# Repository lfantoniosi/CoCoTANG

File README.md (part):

# CoCoTANG

## Overview

CoCoTANG upgrades the Radio Shack/Tandy Color Computer 1 and 2 with a Tang Nano 20K FPGA board and CoCo 3 video and memory features. It retains the MC6809E CPU and motherboard PIAs while the FPGA implements the GIME video and memory subsystem, HDMI and analog video outputs, and a Glenside-compatible IDE interface backed by a microSD card. It also provides 8 MB of RAM, Orchestra-90 audio with stereo over HDMI, and Tandy Speech/Sound Cartridge (SSC) support.

This repository contains the FPGA sources, KiCad designs, fabrication files, and bill of materials.

The assembly uses a **main board** for the CPU and Tang Nano 20K, **PIA0 and PIA1 adapter boards**, and an **address mux board** that replaces the motherboard 74LS138. An **analog video hat** and an **HDB-DOS ROM cartridge** are optional. The render above shows the boards arranged as a PCB panel. HDB-DOS can also be supplied through an FD-502 ROM socket or CoCo SDC flash bank.

The design uses NTSC machine clocking. The GIME's 50 Hz setting remains available, but selecting it does **not** switch to a PAL crystal. PAL-encoded CVBS/S-Video output is also supported. See [Build on macOS or Linux](#build-on-macos-or-linux) for video targets and the [FPGA pin and bus map](fpga/docs/pinout.md) for hardware connections.

## Compatibility

### Color Computer 1 power-supply noise

CoCoTANG has been confirmed working on a Color Computer 1 with added power-supply decoupling: **a 100 µF electrolytic capacitor and a 100 nF ceramic capacitor connected in parallel across the supply**, as shown below. This resolves the power-supply noise that previously caused rolling video interference and intermittent loss of analog sync, and also appeared to affect HDMI.

### Games

So far, **The Contras is the only game found to fail to load in its original form**. CoCoTANG's **262.5-scanline timing drifts relative to the original CoCo 3**. The resulting timing difference affects an unprotected code section in the game and prevents the original version from loading.

Use the [patched version of The Contras](https://drive.google.com/file/d/1ANGJpljmbaEt34lFBowtTOSvq0qSiGtF/view?usp=sharing) instead. This patched version also includes **keyboard enhancements**.

### Multi-Pak Interface and real floppy drives

A **Multi-Pak Interface (MPI)** holds the cartridge data bus in a way that prevents access to CoCoTANG's internal peripheral registers. With an MPI connected, the **internal Glenside IDE, SSC sound/speech, and Orchestra-90 are unavailable**. Software that uses these internal devices must be run without the MPI.

**An MPI is required to use real floppy drives.** Plug the floppy disk controller into the MPI and connect the drives to that controller. This setup uses the external floppy controller, with the internal IDE, SSC, and Orchestra-90 unavailable as described above.

## Current FPGA features

- GIME video and memory mapping with 8 MB NoCan3-style RAM support and readable Disto MMU page bits.
- Simultaneous HDMI and analog video, with separate RGB, YPbPr, and CVBS/S-Video build targets.
- Six motherboard RESET selections combining normal, reversed, or disabled artifact colours with SSC sound/speech off or on.
- Tandy Speech/Sound Cartridge PSG, buffered allophones, and ASCII English text-to-speech, alongside the CoCo DAC and Orchestra-90 audio.
- HDMI status labels and an optional analog status banner with a larger font.

## Hardware and files

| Item | File or notes |
| --- | --- |
| PCB fabrication files | [Gerber/drill ZIPs for each board](kicad/gerber/) |
| KiCad schematic and PCB | [kicad/](kicad/) |
| Components | Full bill of materials below |
| FPGA project and sources | [fpga/](fpga/) |
| FPGA pin/bus map | [fpga/docs/pinout.md](fpga/docs/pinout.md) |

## Board quantities and Gerber downloads

For one CoCoTANG installation, you need **one main board, one address mux board, and two PIA boards**: one for PIA0 and one for PIA1. There are two main-board versions, for motherboard revisions **20261043** and **20261058**; choose the version that matches your motherboard. The HDB-DOS cartridge and video hat are optional.

| Board | Quantity per installation | Gerber/drill ZIP |
| --- | --- | --- |
| Main board (CPU / Tang Nano 20K) | 1 required; choose the matching version | See the compatibility table below |
| Address mux (addrmux) | 1 required | [gerber_addrmux.zip](kicad/gerber/gerber_addrmux.zip) |
| PIA card | 2 required: PIA0 and PIA1 | [gerber_pia.zip](kicad/gerber/gerber_pia.zip) |
| HDB-DOS cartridge | 1 optional | [gerber_cart.zip](kicad/gerber/gerber_cart.zip) |
| Video hat | 1 optional | [gerber_avideo.zip](kicad/gerber/gerber_avideo.zip) |
| External keyboard extension | 1 optional | [gerber_extkey.zip](kicad/gerber/gerber_extkey.zip) |

Use the same PIA Gerber ZIP to fabricate both PIA cards. Upload each desired board's ZIP separately to your PCB manufacturer and select the quantities above, subject to the manufacturer's minimum order quantity.

Select **1.2 mm PCB thickness** when ordering the adapter boards. The thinner boards reduce the installed profile and help the assembly fit under the keyboard.

## Motherboard compatibility

Tandy used several motherboard layouts for the CoCo 2. Identify your motherboard before ordering boards: the CPU and address mux adapters must fit its layout. Only the revisions marked compatible below are currently supported; other layouts may need different adapters.

| Motherboard revision | Compatible | Main board Gerber ZIP |
| --- | --- | --- |
| [20261043](fpga/docs/20261043.jpg) | Yes | [gerber_main_20261043.zip](kicad/gerber/gerber_main_20261043.zip) |
| [20261058](fpga/docs/20261058.jpg) | Yes | [gerber_main_20261058.zip](kicad/gerber/gerber_main_20261058.zip) |
| [20261044](fpga/docs/20261044.jpg) | No | — |
| [20261045](fpga/docs/20261045.jpg) | No | — |
| [20261059](fpga/docs/20261059.jpg) | No | — |

**CoCo 1 operation is confirmed with added 100 µF + 100 nF supply decoupling.** See the [decoupling details and installation photo](#color-computer-1-power-supply-noise).

## Bill of materials

Both main-board versions (**20261043** and **20261058**) use the same components and quantities; only the PCB layout differs. Use the fabrication drawing and silkscreen for the version you are assembling.

### Logic families and supply voltages

Use **HCT** parts for the 5 V logic: U9/U16 (74HCT245, depending on the main-board version), U1 (74HCT138), U22 (74HCT11), and U7 (74HCT30). Their TTL-compatible inputs accept the logic levels used at the motherboard interface. The table below gives the manufacturer part numbers, matching DigiKey part numbers, and TSSOP packages.

**U3/U6 are 74HC139 decoders powered from 3.3 V**, with their select inputs driven by the FPGA. Keep the HC version here: [74HCT139 is specified for a 4.5–5.5 V supply](https://assets.nexperia.com/documents/data-sheet/74HC_HCT139.pdf). A 3.3 V supply makes HC139 suitable for this 3.3 V logic domain; it does not turn HC into a generally TTL-compatible family. The KiCad labels now identify both decoder instances as HC139.

The four **74LVC245** buffers on each main board remain LVC parts for the 3.3 V interface; their reference designators are listed for both layouts below. Their TSSOP ordering code is **SN74LVC245APWR**.

### Main board — both versions

The reference columns identify the same components on each layout. Lists follow the same order across both columns. The three interrupt/reset resistors and the additional R/W pull-up are listed separately. The other adapter boards below are shared between both versions.

| Qty | Value | Description | DigiKey P/N | 20261043 references | 20261058 references | Alternative link |
| ---: | --- | --- | --- | --- | --- | --- |
| 1 | Tang Nano 20K | Tang Nano 20K FPGA Board | N/A | U5 | U17 | [AliExpress](https://www.aliexpress.com/item/1005010280135538.html) |
| 6 | 0.1 µF | CAP CER 0805 0.1UF 100VDC X7R | [399-C0805F104K1RACAUTOCT-ND](https://www.digikey.com/en/products/detail/kemet/C0805F104K1RACAUTO/26735352) | C2, C3, C4, C5, C6, C7 | C13, C16, C19, C14, C18, C15 |  |
| 3 | MMBT3904-TP | TRANS NPN 40V 0.2A SOT-23 | [MMBT3904TPMSCT-ND](https://www.digikey.com/en/products/detail/mcc-micro-commercial-components/MMBT3904-TP/717280) | Q7, Q8, Q9 | Q1, Q3, Q6 |  |
| 1 | SS14 | DIODE SCHOTTKY 40V 1A DO214AC | [SS14CT-ND](https://www.digikey.com/en/products/detail/onsemi/SS14/965474) | D2 | D4 |  |
| 3 | 10K | RES 10K OHM 1% 1/8W 0805 | [311-10.0KCRCT-ND](https://www.digikey.com/en/products/detail/yageo/RC0805FR-0710KL/727535) | R2, R4, R6 | R14, R18, R15 |  |
| 3 | 4.7K | RES 4.7K OHM 1% 1/8W 0805 | [311-4.70KCRCT-ND](https://www.digikey.com/en/products/detail/yageo/RC0805FR-074K7L/730876) | R3, R5, R7 | R20, R22, R21 |  |
| 1 | 4.7K | R/W pull-up, 1% 1/8W 0805 | [311-4.70KCRCT-ND](https://www.digikey.com/en/products/detail/yageo/RC0805FR-074K7L/730876) | R19 | R13 |  |
| 2 | 47K | RES SMD 47K OHM 1% 1/8W 0805 | [YAG3735CT-ND](https://www.digikey.com/en/products/detail/yageo/AC0805FR-0747KL/6006584) | R8, R9 | R25, R26 |  |
| 2 | 4.7K | RES ARRAY 8 RES 4.7K OHM 9SIP | [4609X-101-472LF-ND](https://www.digikey.ca/en/products/detail/bourns-inc/4609X-101-472LF/3593671) | RN1, RN2 | RN4, RN3 |  |
| 4 | SN74LVC245APWR | 8-bit bus transceiver, 1.65–3.6 V, TSSOP-20 | [296-1233-1-ND](https://www.digikey.com/en/products/detail/texas-instruments/SN74LVC245APWR/276501) | U8, U10, U11, U12 | U4, U13, U15, U14 |  |
| 1 | SN74HCT245PWR | 8-bit bus transceiver, TTL inputs, 4.5–5.5 V, TSSOP-20 | [296-8404-1-ND](https://www.digikey.com/en/products/detail/texas-instruments/SN74HCT245PWR/376998) | U9 | U16 |  |
| 1 | 74HC139PW,118 | Dual 2-to-4 decoder, CMOS inputs, 2–6 V; used at 3.3 V, TSSOP-16 | [1727-6580-1-ND](https://www.digikey.com/en/products/detail/nexperia-usa-inc/74HC139PW-118/2813773) | U3 | U6 |  |
| 1 | SIL FEMALE HDR | MACHINE PIN SOCKET 40P 2.54MM PI | [SMC-1A-40-1-GT-HT](https://www.digikey.com/en/products/detail/adam-tech/SMC-1A-40-1-GT-HT/9831942) | U5 | U17 | [AliExpress](https://www.aliexpress.com/item/1005008648234734.html) |
| 1 | DIP-40 SOCKET | MACHINE PIN SOCKET, IC, DIP, 40P | [ICM-640-1-GT-HT](https://www.digikey.com/en/products/detail/adam-tech/ICM-640-1-GT-HT/9832971) | J1 | J19 | [AliExpress](https://www.aliexpress.com/item/1005006139495909.html) |

### PIA0 adapter

| Qty | Value | Description | DigiKey P/N | References | Alternative link |
| ---: | --- | --- | --- | --- | --- |
| 1 | 0.1 µF | CAP CER 0805 0.1UF 100VDC X7R | [399-C0805F104K1RACAUTOCT-ND](https://www.digikey.com/en/products/detail/kemet/C0805F104K1RACAUTO/26735352) | C1 | |
| 1 | DIP-40 SOCKET | MACHINE PIN SOCKET, IC, DIP, 40P | [ICM-640-1-GT-HT](https://www.digikey.com/en/products/detail/adam-tech/ICM-640-1-GT-HT/9832971) | J4 | [AliExpress](https://www.aliexpress.com/item/1005006139495909.html) |
| 1 | 74HCT30PW,118 | 8-input NAND gate, TTL inputs, 4.5–5.5 V, TSSOP-14 | [1727-6632-1-ND](https://www.digikey.com/en/products/detail/nexperia-usa-inc/74HCT30PW-118/1230819) | U7 | |
| 2 | 1,800 pF | CAP CER 1800PF 250V C0G/NP0 0805 | [490-GCM21A5C2E182FX01DCT-ND](https://www.digikey.ca/en/products/detail/murata-electronics/GCM21A5C2E182FX01D/17845644) | C10,C12 | |
| 2 | SD103BW | DIODE SCHOTTKY 30V 0.35A SOD123F | [4878-SD103BWCT-ND](https://www.digikey.com/en/products/detail/diotec-semiconductor/SD103BW/22600375) | D1,D3 | |

### PIA1 adapter

| Qty | Value | Description | DigiKey P/N | References | Alternative link |
| ---: | --- | --- | --- | --- | --- |
| 1 | DIP-40 SOCKET | MACHINE PIN SOCKET, IC, DIP, 40P | [ICM-640-1-GT-HT](https://www.digikey.com/en/products/detail/adam-tech/ICM-640-1-GT-HT/9832971) | J4 | [AliExpress](https://www.aliexpress.com/item/1005006139495909.html) |

### Address mux board

| Qty | Value | Description | DigiKey P/N | References | Alternative link |
| ---: | --- | --- | --- | --- | --- |
| 2 | 0.1 µF | CAP CER 0805 0.1UF 100VDC X7R | [399-C0805F104K1RACAUTOCT-ND](https://www.digikey.com/en/products/detail/kemet/C0805F104K1RACAUTO/26735352) | C32,C33 | |
| 1 | SN74HCT138PWR | 3-to-8 decoder, TTL inputs, 4.5–5.5 V, TSSOP-16 | [296-8388-1-ND](https://www.digikey.com/en/products/detail/texas-instruments/SN74HCT138PWR/377055) | U1 | |
| 1 | 74HCT11PW,118 | Triple 3-input AND gate, TTL inputs, 4.5–5.5 V, TSSOP-14 | [1727-7964-1-ND](https://www.digikey.com/en/products/detail/nexperia-usa-inc/74HCT11PW-118/1230602) | U22 | |
| 1 | DIP-16 SOCKET | CONN IC DIP SOCKET 16POS GOLD | [SA163000](https://www.digikey.com/en/products/detail/on-shore-technology-inc/SA163000/3313525) | J28 | [AliExpress](https://www.aliexpress.com/item/32866483409.html) |

### HDB-DOS cartridge

| Qty | Value | Description | DigiKey P/N | References | Alternative link |
| ---: | --- | --- | --- | --- | --- |
| 1 | DIP-28 SOCKET | CONN IC DIP SOCKET 28POS GOLD | [110-41-628-41-001000](https://www.digikey.com/en/products/detail/mill-max-manufacturing-corp/110-41-628-41-001000/2538108) | U2 | [AliExpress](https://www.aliexpress.com/item/32866483409.html) |
| 1 | 0.1 µF | CAP CER 0805 0.1UF 100VDC X7R | [399-C0805F104K1RACAUTOCT-ND](https://www.digikey.com/en/products/detail/kemet/C0805F104K1RACAUTO/26735352) | C34 | |
| 1 | AT28C64B-15PU | IC EEPROM 64KBIT PARALLEL 28DIP | [AT28C64B-15PU-ND](https://www.digikey.com/en/products/detail/microchip-technology/AT28C64B-15PU/1008529) | U2 | |

### Analog video board

| Qty | Value | Description | DigiKey P/N | References | Alternative link |
| ---: | --- | --- | --- | --- | --- |
| 3 | 0.1 µF | CAP CER 0805 0.1UF 100VDC X7R | [399-C0805F104K1RACAUTOCT-ND](https://www.digikey.com/en/products/detail/kemet/C0805F104K1RACAUTO/26735352) | C29,C30,C31 | |
| 3 | 470 pF | CAP CER 470PF 50V C0G/NP0 0805 | [490-1617-1-ND](https://www.digikey.com/en/products/detail/murata-electronics/GRM2165C1H471JA01D/587515) | C8,C9,C11 | |
| 1 | 1 µF | CAP CER 1UF 25V X7R 0805 | [399-C0805C105K3RACTUCT-ND](https://www.digikey.com/en/products/detail/kemet/C0805C105K3RACTU/3471727) | C15 | |
| 6 | 1K | RES 1K OHM 1% 1/8W 0805 | [541-3977-1-ND](https://www.digikey.com/en/products/detail/vishay-dale/CRCW08051K00FKEAC/7928660) | R31,R17,R33,R1,R35,R16 | |
| 3 | 75 | RES 75 OHM 1% 1/8W 0805 | [541-CRCW080575R0FKEACCT-ND](https://www.digikey.com/en/products/detail/vishay-dale/CRCW080575R0FKEAC/12745060) | R10,R11,R12 | |
| 3 | 4.7K | RES 4.7K OHM 1% 1/8W 0805 | [311-4.70KCRCT-ND](https://www.digikey.com/en/products/detail/yageo/RC0805FR-074K7L/730876) | R32,R34,R36 | |
| 1 | 6.8 nF | CAP CER 6800PF 250V C0G/NP0 0805 | [490-GCM21B5C2E682JX0ALCT-ND](https://www.digikey.com/en/products/detail/murata-electronics/GCM21B5C2E682JX0AL/17846799) | C24 | |
| 1 | 4.7 µF | CAP CER 4.7UF 16V X7R 0805 | [732-7666-1-ND](https://www.digikey.com/en/products/detail/w%C3%BCrth-elektronik/885012207053/5453521) | C25 | |
| 1 | 100K | RES 100K OHM 1% 1/8W 0805 | [541-3978-1-ND](https://www.digikey.com/en/products/detail/vishay-dale/CRCW0805100KFKEAC/7928661) | R24 | |
| 3 | MMBT3904-TP | TRANS NPN 40V 0.2A SOT-23 | [MMBT3904TPMSCT-ND](https://www.digikey.com/en/products/detail/mcc-micro-commercial-components/MMBT3904-TP/717280) | Q2,Q4,Q5 | |
| 1 | DIN-5 FEMALE | D5 PIN DIN SOCKET 180 DEGREE | [4654-FC680805-ND](https://www.digikey.ca/en/products/detail/cliff-electronic-components-ltd/FC680805/24420883) | J24 | [AliExpress](https://www.aliexpress.com/item/32981543684.html)|

## Boards Interconnection
| Qty | Value | Description | DigiKey P/N | References | Alternative link |
| ---: | --- | --- | --- | --- | --- |
| 2 | PRPC040SBAN-M71RC | CONN HEADER R/A 40POS 2.54MM | [S1111EC-40-ND](https://www.digikey.ca/en/products/detail/sullins-connector-solutions/PRPC040SBAN-M71RC/2775294) | 
| 2 |1950 | JUMPER WIRE F TO F 6" 28AWG | [1528-1961-ND](https://www.digikey.ca/en/products/detail/adafruit-industries-llc/1950/6827084)

*NOTE:* You may need more than one jumper wires pack or source at different place like Amazon. CoCo1 requires longer jumper wires  

## Assembly

Print the [fabrication drawing](fpga/docs/fab.pdf) and use it with the board silkscreen to identify component positions. Check diode orientation before soldering. The main-board bill of materials applies to both supported versions; component positions differ between layouts.

Several adapters have oversized socket holes. They require machined-pin sockets whose pins extend through the adapter to connect to the motherboard socket while holding the original IC above it. Use 1.2 mm PCBs to reduce the overall assembly height and improve clearance under the keyboard.

1. Locate and desolder the CPU, VDG, SAM, PIA0, PIA1, and 74LS138.
2. Keep the SAM, VDG, and 74LS138 as spares; the FPGA replaces their functions.
3. Install sockets in the motherboard. Do not solder the adapter boards directly to it.
4. Check clearance around the adapters. Some original capacitors marked `104` are oversized, and nearby radial capacitors may also interfere. Where necessary, desolder and reposition their leads before bending the capacitors closer to the motherboard.
5. Populate the adapter boards, checking diode orientation. Configure each PIA adapter as described in [PIA adapter configuration](#pia-adapter-configuration).
6. Modify pin 5 of each joystick connector and wire it to the PIA0 adapter as described in [Joystick second-button support](#joystick-second-button-support).
7. Fit the CPU and PIAs to their adapters, install the adapters, and connect the boards as shown in the [installed prototype](fpga/docs/installed_prototype.jpg).
8. Program the Tang Nano 20K with the desired `.fs` bitstream and CoCo 3 ROM, following the programming instructions below.
9. If using the optional HDB-DOS cartridge, program its EEPROM with [hdblba.rom](fpga/roms/hdblba.rom) using an EEPROM programmer.
10. Turn on the computer. The boot screen should look like the example below.

### Assembled boards

The photos below show the component population and header placement, in assembly order. Front and back views are included where available.

#### Main board

The main board carries the CPU socket, Tang Nano 20K headers, bus buffers, and connections to the other adapters. The photos show the assembled board before fitting the CPU and FPGA module. Choose the layout that matches your motherboard revision.

| Front | Back |
| --- | --- |
|  |  |

#### ADDRMUX board

The address mux adapter plugs into the motherboard's former **74LS138** position and connects to the main board. **Leave the 74LS138 socket on the ADDRMUX adapter empty; do not reinstall the original IC in it.** The adapter's onboard logic replaces its function.

#### PIA0 adapter

Populate the logic IC, diodes, capacitors, and headers required for PIA0, and select the **PIA0** jumper setting. The external keyboard header is fitted only on this adapter. These photos show the board before installing the PIA.

| Front | Back |
| --- | --- |
|  |  |

#### PIA1 adapter

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
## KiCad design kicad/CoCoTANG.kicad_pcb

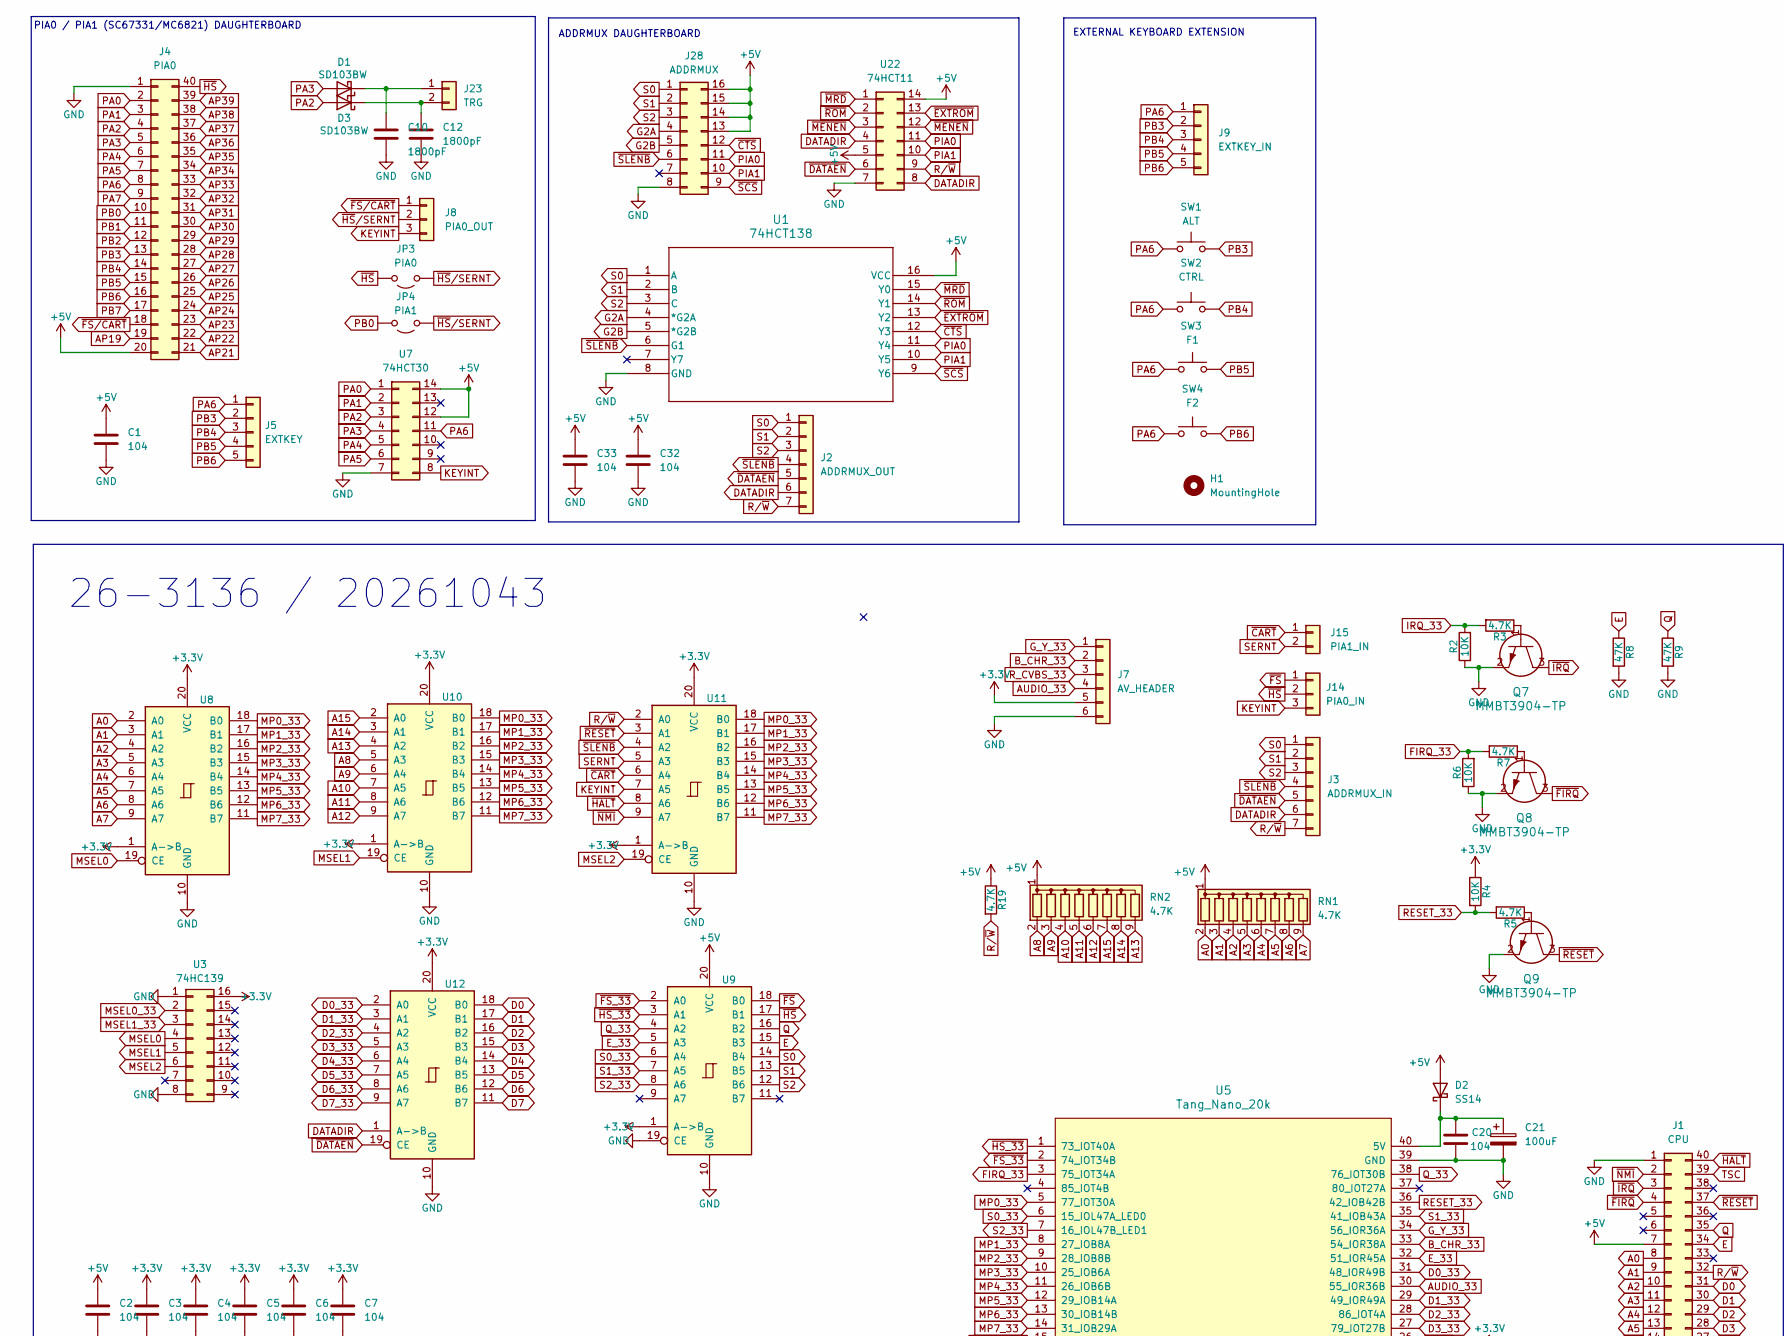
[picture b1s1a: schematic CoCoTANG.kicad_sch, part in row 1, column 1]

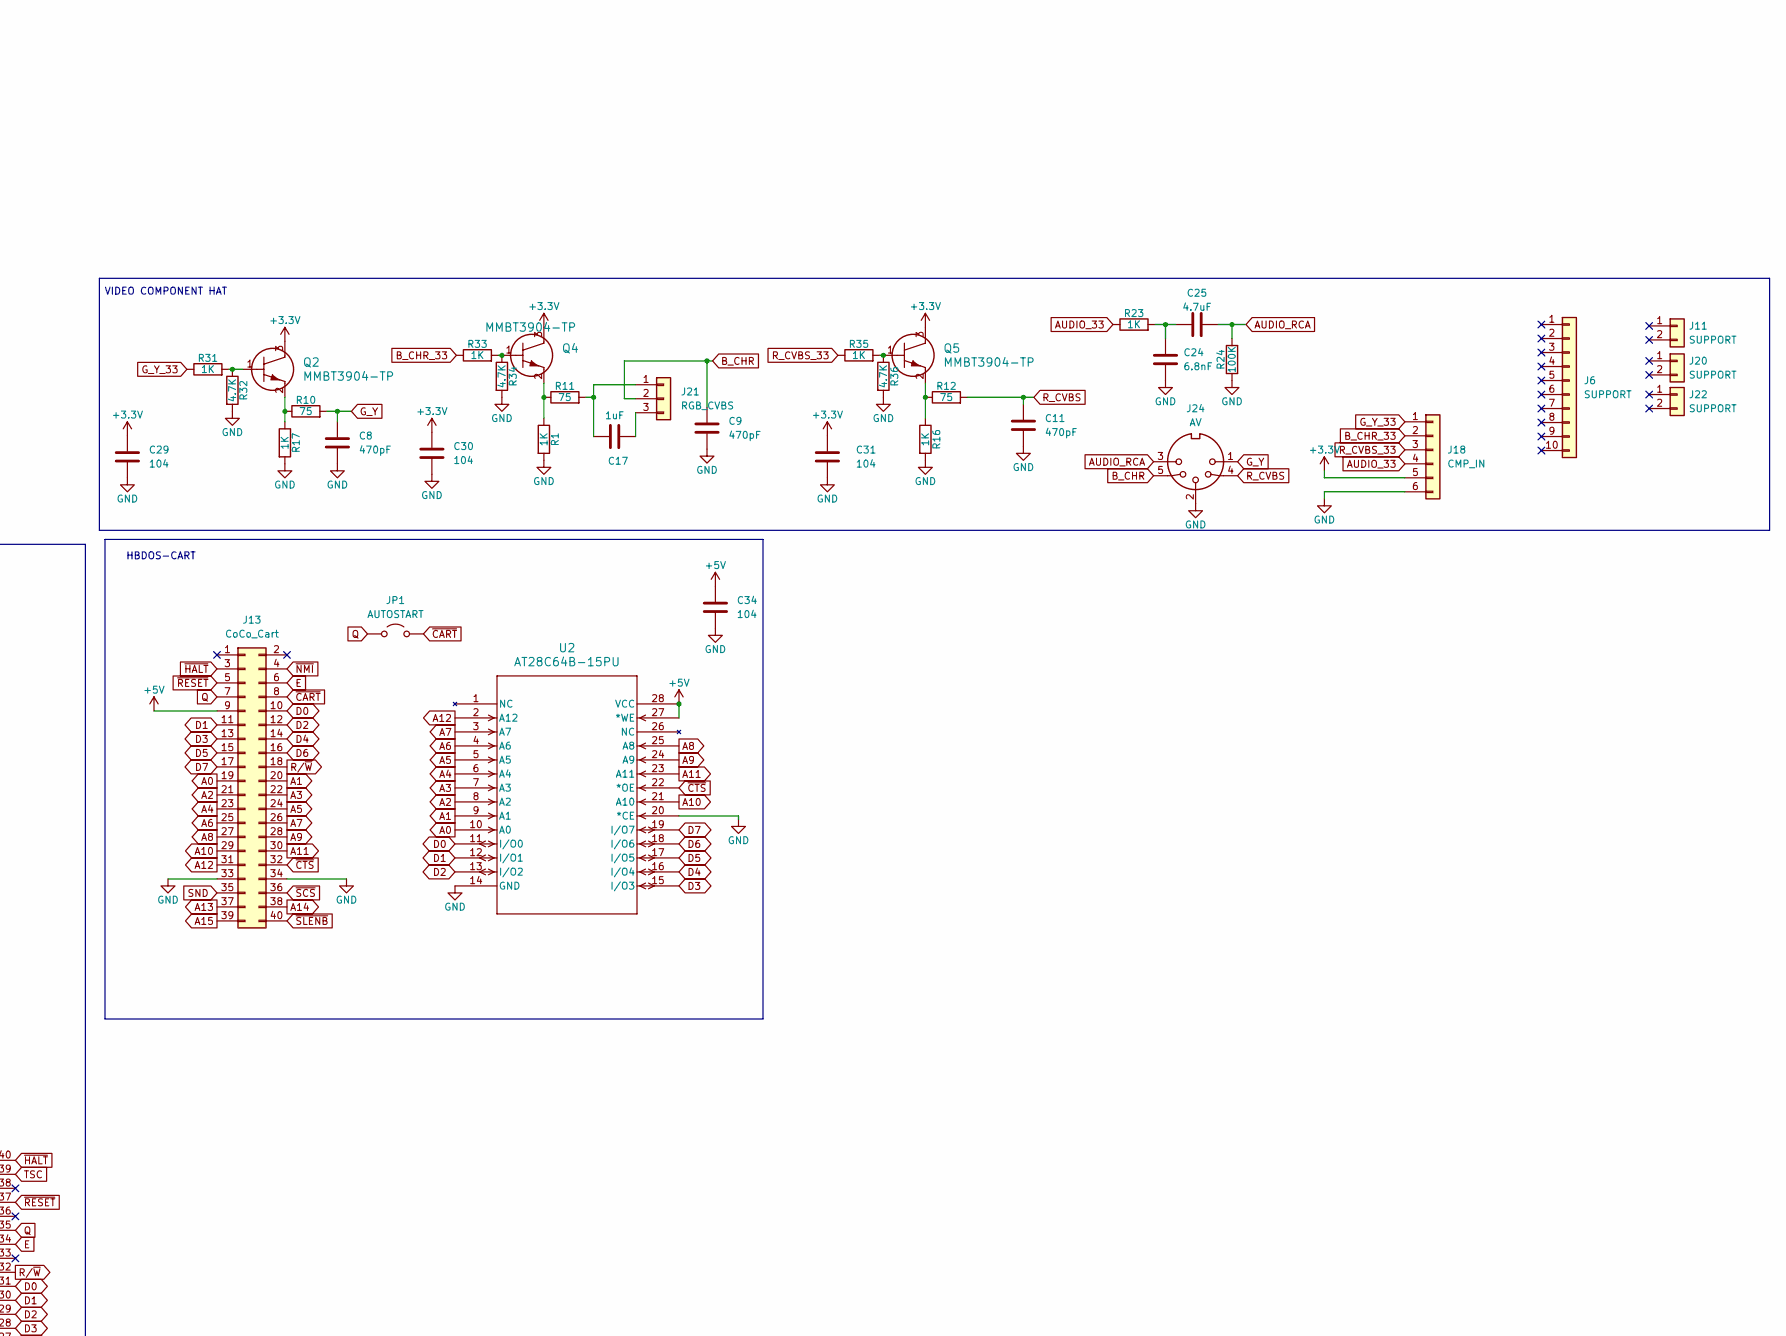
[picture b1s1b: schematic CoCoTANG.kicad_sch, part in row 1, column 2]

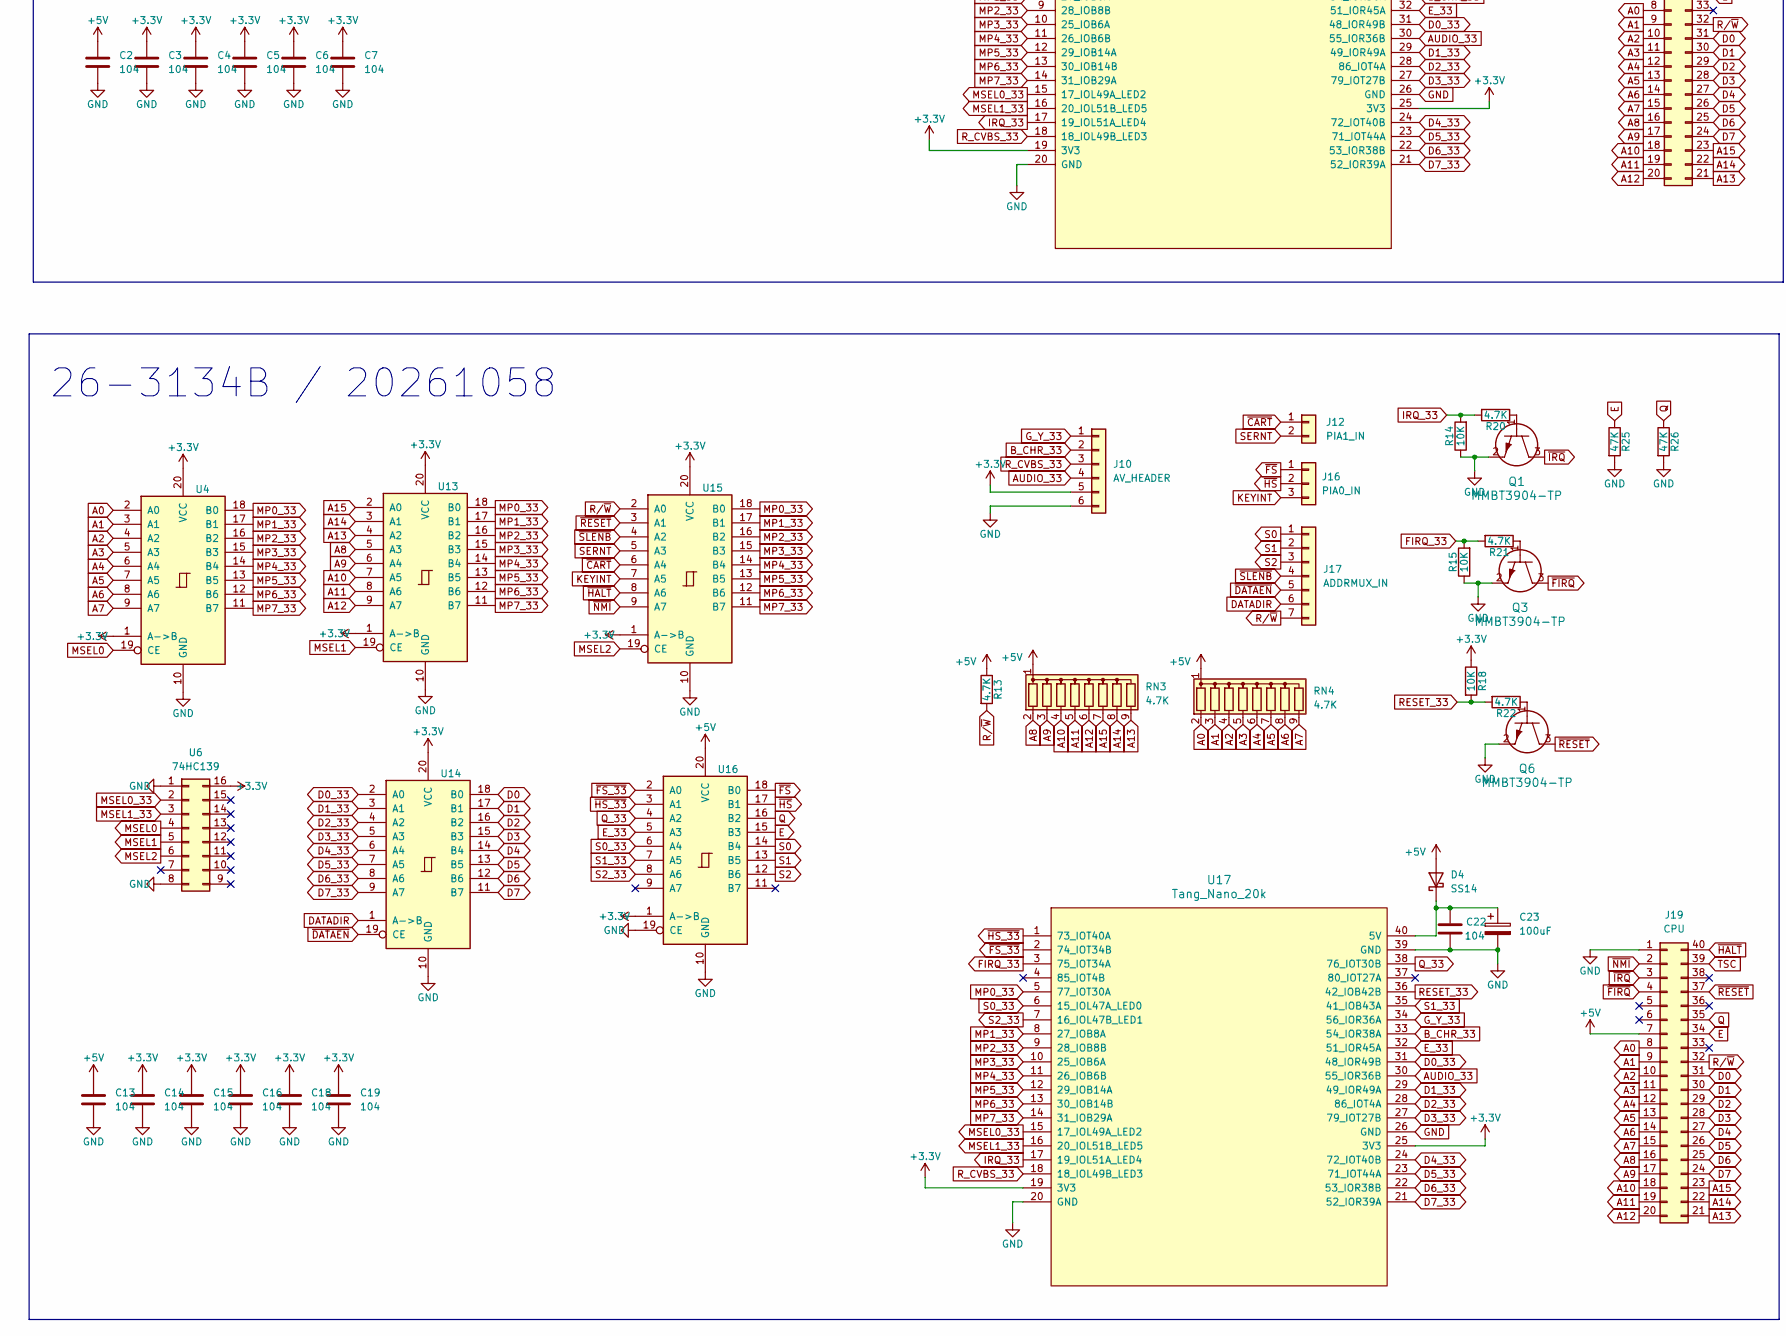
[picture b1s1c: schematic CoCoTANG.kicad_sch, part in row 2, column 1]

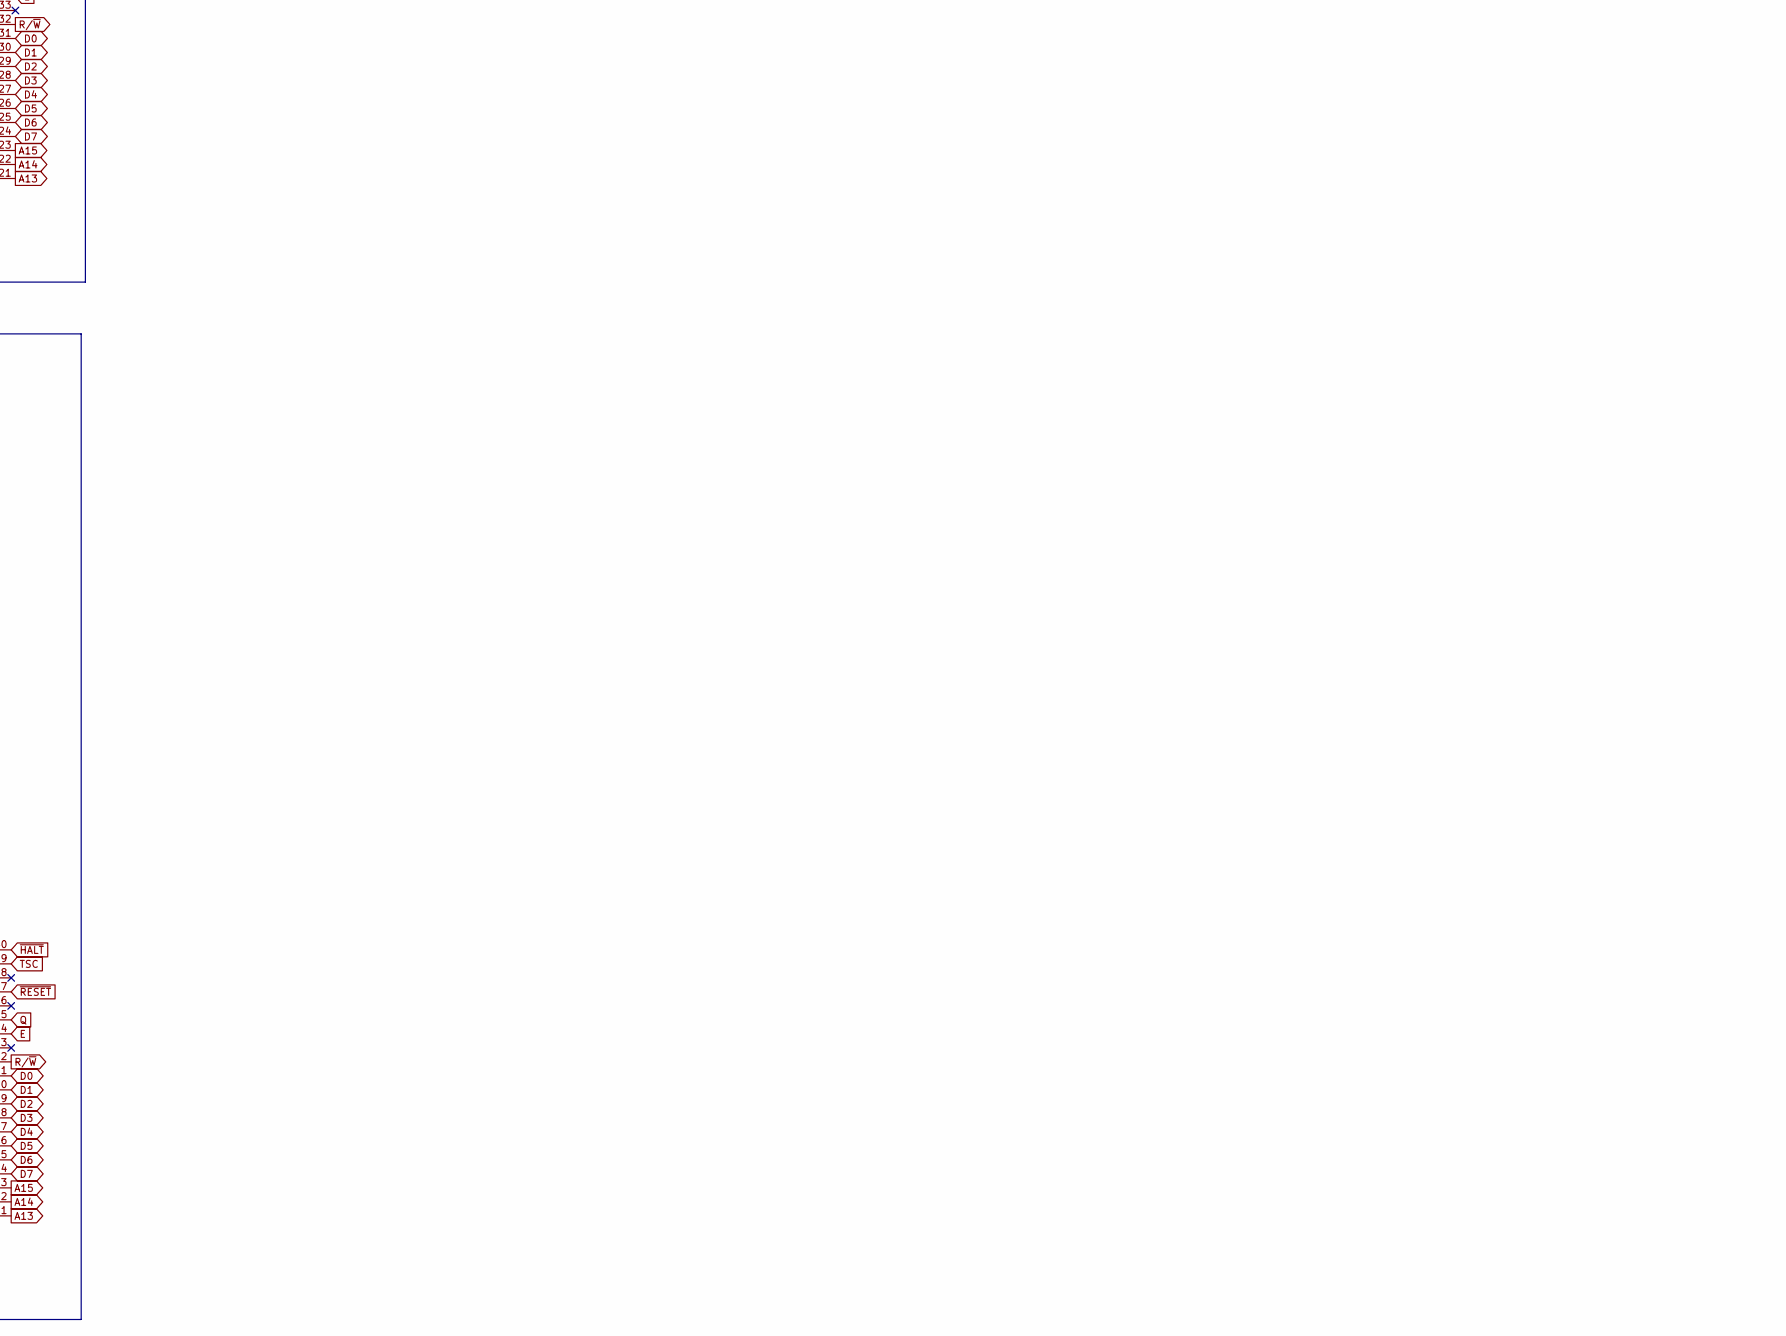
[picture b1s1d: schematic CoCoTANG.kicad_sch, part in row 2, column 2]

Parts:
C1, C2, C3, C4, C5, C6, C7, C13, C14, C15, C16, C18, C19, C20, C22, C29, C30, C31, C32, C33, C34: 104; C_0805_2012Metric_Pad1.18x1.45mm_HandSolder
C8, C9, C11: 470pF; C_0805_2012Metric_Pad1.18x1.45mm_HandSolder
C10, C12: 1800pF; C_0805_2012Metric_Pad1.18x1.45mm_HandSolder
C17: 1uF; C_0805_2012Metric_Pad1.18x1.45mm_HandSolder
C21, C23: 100uF; CP_Radial_D5.0mm_P2.50mm
C24: 6.8nF; C_0805_2012Metric_Pad1.18x1.45mm_HandSolder
C25: 4.7uF; C_0805_2012Metric_Pad1.18x1.45mm_HandSolder
D1, D3: SD103BW; D_SOD-123F
D2, D4: SS14; D_SMA
H1: MountingHole; MountingHole_4.3mm_M4
J1, J19: CPU; DIP-40_W15.24mm-OVERSIZED
J2: ADDRMUX_OUT; PinHeader_1x07_P2.54mm_Vertical
J3, J17: ADDRMUX_IN; PinHeader_1x07_P2.54mm_Vertical
J4: PIA0; DIP-40_W15.24mm-OVERSIZED
J5: EXTKEY; PinSocket_1x05_P2.54mm_Vertical
J6: SUPPORT; PinHeader_1x10_P2.54mm_Vertical
J7, J10: AV_HEADER; PinSocket_1x06_P2.54mm_Vertical
J8: PIA0_OUT; PinHeader_1x03_P2.54mm_Vertical
J9: EXTKEY_IN; PinSocket_1x05_P2.54mm_Vertical
J11, J20, J22: SUPPORT; PinSocket_1x02_P2.54mm_Vertical
J12, J15: PIA1_IN; PinHeader_1x02_P2.54mm_Vertical
J13: CoCo_Cart; COCO_CART
J14, J16: PIA0_IN; PinHeader_1x03_P2.54mm_Vertical
J18: CMP_IN; PinHeader_1x06_P2.54mm_Vertical
J21: RGB_CVBS; PinSocket_1x03_P2.54mm_Vertical
J23: TRG; PinHeader_1x02_P2.54mm_Vertical
J24: AV; SWITCHCRAFT_57PC5F
J28: ADDRMUX; DIP-16_W7.62mm-OVERSIZED
JP1: AUTOSTART; SolderJumper-2_P1.3mm_Open_Pad1.0x1.5mm
JP3: PIA0; SolderJumper-2_P1.3mm_Open_Pad1.0x1.5mm
JP4: PIA1; SolderJumper-2_P1.3mm_Open_Pad1.0x1.5mm
Q1, Q2, Q3, Q4, Q5, Q6, Q7, Q8, Q9: MMBT3904-TP; SOT-23_MCC
R1, R16, R17, R23, R31, R33, R35: 1K; R_0805_2012Metric_Pad1.20x1.40mm_HandSolder
R2, R4, R6, R14, R15, R18: 10K; R_0805_2012Metric_Pad1.20x1.40mm_HandSolder
R3, R5, R7, R13, R19, R20, R21, R22, R32, R34, R36: 4.7K; R_0805_2012Metric_Pad1.20x1.40mm_HandSolder
R8, R9, R25, R26: 47K; R_0805_2012Metric_Pad1.20x1.40mm_HandSolder
R10, R11, R12: 75; R_0805_2012Metric_Pad1.20x1.40mm_HandSolder
R24: 100K; R_0805_2012Metric_Pad1.20x1.40mm_HandSolder
RN1, RN2, RN3, RN4: 4.7K; R_Array_SIP9
SW1: ALT; SW_Cherry_MX_1.00u_PCB
SW2: CTRL; SW_Cherry_MX_1.00u_PCB
SW3: F1; SW_Cherry_MX_1.00u_PCB
SW4: F2; SW_Cherry_MX_1.00u_PCB
U1: 74HCT138; TSSOP-16_4.4x5mm_P0.65mm
U2: AT28C64B-15PU; 28P6_ATM
U3, U6: 74HC139; TSSOP-16_4.4x5mm_P0.65mm
U4, U8, U10, U11, U12, U13, U14, U15: 74LVC245; TSSOP-20_4.4x6.5mm_P0.65mm
U5, U17: Tang_Nano_20k
U7: 74HCT30; TSSOP-14_4.4x5mm_P0.65mm
U9, U16: 74HCT245; TSSOP-20_4.4x6.5mm_P0.65mm
U22: 74HCT11; TSSOP-14_4.4x5mm_P0.65mm

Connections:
+3.3V: C3.1, C4.1, C5.1, C6.1, C7.1, C14.1, C15.1, C16.1, C18.1, C19.1, C29.1, C30.1, C31.1, J7.5, J10.5, J18.5, Q2.3, Q4.3, Q5.3, R4.1, R18.1, U3.16, U4.1 (A->B), U4.20 (VCC), U5.19 (3V3), U5.25 (3V3), U6.16, U8.1 (A->B), U8.20 (VCC), U9.1 (A->B), U10.1 (A->B), U10.20 (VCC), U11.1 (A->B), U11.20 (VCC), U12.20 (VCC), U13.1 (A->B), U13.20 (VCC), U14.20 (VCC), U15.1 (A->B), U15.20 (VCC), U16.1 (A->B), U17.19 (3V3), U17.25 (3V3)
+5V: C1.1, C2.1, C13.1, C32.1, C33.1, C34.1, D2.2 (A), D4.2 (A), J1.7, J4.20, J13.9, J19.7, J28.13, J28.14, J28.15, J28.16, R13.1, R19.1, RN1.1 (common), RN2.1 (common), RN3.1 (common), RN4.1 (common), U1.16 (VCC), U2.27 (*WE), U2.28 (VCC), U7.12, U7.14, U9.20 (VCC), U16.20 (VCC), U22.5, U22.14
A0: J1.8, J13.19, J19.8, RN1.2 (R1), RN4.2 (R1), U2.10 (A0), U4.2 (A0), U8.2 (A0)
A1: J1.9, J13.20, J19.9, RN1.3 (R2), RN4.3 (R2), U2.9 (A1), U4.3 (A1), U8.3 (A1)
A2: J1.10, J13.21, J19.10, RN1.4 (R3), RN4.4 (R3), U2.8 (A2), U4.4 (A2), U8.4 (A2)
A3: J1.11, J13.22, J19.11, RN1.5 (R4), RN4.5 (R4), U2.7 (A3), U4.5 (A3), U8.5 (A3)
A4: J1.12, J13.23, J19.12, RN1.6 (R5), RN4.6 (R5), U2.6 (A4), U4.6 (A4), U8.6 (A4)
A5: J1.13, J13.24, J19.13, RN1.7 (R6), RN4.7 (R6), U2.5 (A5), U4.7 (A5), U8.7 (A5)
A6: J1.14, J13.25, J19.14, RN1.8 (R7), RN4.8 (R7), U2.4 (A6), U4.8 (A6), U8.8 (A6)
A7: J1.15, J13.26, J19.15, RN1.9 (R8), RN4.9 (R8), U2.3 (A7), U4.9 (A7), U8.9 (A7)
A8: J1.16, J13.27, J19.16, RN2.2 (R1), RN3.2 (R1), U2.25 (A8), U10.5 (A3), U13.5 (A3)
A9: J1.17, J13.28, J19.17, RN2.3 (R2), RN3.3 (R2), U2.24 (A9), U10.6 (A4), U13.6 (A4)
A10: J1.18, J13.29, J19.18, RN2.4 (R3), RN3.4 (R3), U2.21 (A10), U10.7 (A5), U13.7 (A5)
A11: J1.19, J13.30, J19.19, RN2.5 (R4), RN3.5 (R4), U2.23 (A11), U10.8 (A6), U13.8 (A6)
A12: J1.20, J13.31, J19.20, RN2.6 (R5), RN3.6 (R5), U2.2 (A12), U10.9 (A7), U13.9 (A7)
A13: J1.21, J13.37, J19.21, RN2.9 (R8), RN3.9 (R8), U10.4 (A2), U13.4 (A2)
A14: J1.22, J13.38, J19.22, RN2.8 (R7), RN3.8 (R7), U10.3 (A1), U13.3 (A1)
A15: J1.23, J13.39, J19.23, RN2.7 (R6), RN3.7 (R6), U10.2 (A0), U13.2 (A0)
AP19: J4.19
AP21: J4.21
AP22: J4.22
AP23: J4.23
AP24: J4.24
AP25: J4.25
AP26: J4.26
AP27: J4.27
AP28: J4.28
AP29: J4.29
AP30: J4.30
AP31: J4.31
AP32: J4.32
AP33: J4.33
AP34: J4.34
AP35: J4.35
AP36: J4.36
AP37: J4.37
AP38: J4.38
AP39: J4.39
AUDIO_33: J7.4, J10.4, J18.4, R23.1, U5.30 (55_IOR36B), U17.30 (55_IOR36B)
AUDIO_RCA: C25.2, J24.3, R24.2
B_CHR: C9.1, J21.2, J24.5
B_CHR_33: J7.2, J10.2, J18.2, R33.1, U5.33 (54_IOR38A), U17.33 (54_IOR38A)
D0: J1.31, J13.10, J19.31, U2.11 (I/O0), U12.18 (B0), U14.18 (B0)
D0_33: U5.31 (48_IOR49B), U12.2 (A0), U14.2 (A0), U17.31 (48_IOR49B)
D1: J1.30, J13.11, J19.30, U2.12 (I/O1), U12.17 (B1), U14.17 (B1)
D1_33: U5.29 (49_IOR49A), U12.3 (A1), U14.3 (A1), U17.29 (49_IOR49A)
D2: J1.29, J13.12, J19.29, U2.13 (I/O2), U12.16 (B2), U14.16 (B2)
D2_33: U5.28 (86_IOT4A), U12.4 (A2), U14.4 (A2), U17.28 (86_IOT4A)
D3: J1.28, J13.13, J19.28, U2.15 (I/O3), U12.15 (B3), U14.15 (B3)
D3_33: U5.27 (79_IOT27B), U12.5 (A3), U14.5 (A3), U17.27 (79_IOT27B)
D4: J1.27, J13.14, J19.27, U2.16 (I/O4), U12.14 (B4), U14.14 (B4)
D4_33: U5.24 (72_IOT40B), U12.6 (A4), U14.6 (A4), U17.24 (72_IOT40B)
D5: J1.26, J13.15, J19.26, U2.17 (I/O5), U12.13 (B5), U14.13 (B5)
D5_33: U5.23 (71_IOT44A), U12.7 (A5), U14.7 (A5), U17.23 (71_IOT44A)
D6: J1.25, J13.16, J19.25, U2.18 (I/O6), U12.12 (B6), U14.12 (B6)
D6_33: U5.22 (53_IOR38B), U12.8 (A6), U14.8 (A6), U17.22 (53_IOR38B)
D7: J1.24, J13.17, J19.24, U2.19 (I/O7), U12.11 (B7), U14.11 (B7)
D7_33: U5.21 (52_IOR39A), U12.9 (A7), U14.9 (A7), U17.21 (52_IOR39A)
DATADIR: J2.6, J3.6, J17.6, U12.1 (A->B), U14.1 (A->B), U22.4, U22.8
E: J1.34, J13.6, J19.34, R8.1, R25.1, U9.15 (B3), U16.15 (B3)
E_33: U5.32 (51_IOR45A), U9.5 (A3), U16.5 (A3), U17.32 (51_IOR45A)
FIRQ_33: R6.2, R7.2, R15.2, R21.2, U5.3 (75_IOT34A), U17.3 (75_IOT34A)
G2A: J28.4, U1.4 (*G2A)
G2B: J28.5, U1.5 (*G2B)
GND: C1.2, C2.2, C3.2, C4.2, C5.2, C6.2, C7.2, C8.2, C9.2, C10.2, C11.2, C12.2, C13.2, C14.2, C15.2, C16.2, C18.2, C19.2, C20.2, C21.2, C22.2, C23.2, C24.1, C29.2, C30.2, C31.2, C32.2, C33.2, C34.2, J1.1, J4.1, J7.6, J10.6, J13.33, J13.34, J18.6, J19.1, J24.2, J28.8, Q1.2, Q3.2, Q6.2, Q7.2, Q8.2, Q9.2, R1.2, R2.1, R6.1, R8.2, R9.2, R14.1, R15.1, R16.2, R17.2, R24.1, R25.2, R26.2, R32.2, R34.2, R36.2, U1.8 (GND), U2.14 (GND), U2.20 (*CE), U3.1, U3.8, U4.10 (GND), U5.20 (GND), U5.26 (GND), U5.39 (GND), U6.1, U6.8, U7.7, U8.10 (GND), U9.10 (GND), U9.19 (CE), U10.10 (GND), U11.10 (GND), U12.10 (GND), U13.10 (GND), U14.10 (GND), U15.10 (GND), U16.10 (GND), U16.19 (CE), U17.20 (GND), U17.26 (GND), U17.39 (GND), U22.7
G_Y: C8.1, J24.1, R10.2
G_Y_33: J7.1, J10.1, J18.1, R31.1, U5.34 (56_IOR36A), U17.34 (56_IOR36A)
IRQ_33: R2.2, R3.2, R14.2, R20.2, U5.17 (19_IOL51A_LED4), U17.17 (19_IOL51A_LED4)
KEYINT: J8.3, J14.3, J16.3, U7.8, U11.7 (A5), U15.7 (A5)
MP0_33: U4.18 (B0), U5.5 (77_IOT30A), U8.18 (B0), U10.18 (B0), U11.18 (B0), U13.18 (B0), U15.18 (B0), U17.5 (77_IOT30A)
MP1_33: U4.17 (B1), U5.8 (27_IOB8A), U8.17 (B1), U10.17 (B1), U11.17 (B1), U13.17 (B1), U15.17 (B1), U17.8 (27_IOB8A)
MP2_33: U4.16 (B2), U5.9 (28_IOB8B), U8.16 (B2), U10.16 (B2), U11.16 (B2), U13.16 (B2), U15.16 (B2), U17.9 (28_IOB8B)
MP3_33: U4.15 (B3), U5.10 (25_IOB6A), U8.15 (B3), U10.15 (B3), U11.15 (B3), U13.15 (B3), U15.15 (B3), U17.10 (25_IOB6A)
MP4_33: U4.14 (B4), U5.11 (26_IOB6B), U8.14 (B4), U10.14 (B4), U11.14 (B4), U13.14 (B4), U15.14 (B4), U17.11 (26_IOB6B)
MP5_33: U4.13 (B5), U5.12 (29_IOB14A), U8.13 (B5), U10.13 (B5), U11.13 (B5), U13.13 (B5), U15.13 (B5), U17.12 (29_IOB14A)
MP6_33: U4.12 (B6), U5.13 (30_IOB14B), U8.12 (B6), U10.12 (B6), U11.12 (B6), U13.12 (B6), U15.12 (B6), U17.13 (30_IOB14B)
MP7_33: U4.11 (B7), U5.14 (31_IOB29A), U8.11 (B7), U10.11 (B7), U11.11 (B7), U13.11 (B7), U15.11 (B7), U17.14 (31_IOB29A)
MSEL0: U3.4, U4.19 (CE), U6.4, U8.19 (CE)
MSEL0_33: U3.2, U5.15 (17_IOL49A_LED2), U6.2, U17.15 (17_IOL49A_LED2)
MSEL1: U3.5, U6.5, U10.19 (CE), U13.19 (CE)
MSEL1_33: U3.3, U5.16 (20_IOL51B_LED5), U6.3, U17.16 (20_IOL51B_LED5)
MSEL2: U3.6, U6.6, U11.19 (CE), U15.19 (CE)
unnamed: C24.2, C25.1, R23.2
unnamed: C10.1, D1.1 (K), J23.1
unnamed: C20.1, C21.1, D2.1 (K), U5.40 (5V)
unnamed: C12.1, D3.1 (K), J23.2
unnamed: C22.1, C23.1, D4.1 (K), U17.40 (5V)
unnamed: C17.1, J21.1, R11.2
unnamed: C17.2, J21.3
unnamed: Q1.1, R20.1
unnamed: Q2.1, R31.2, R32.1
unnamed: Q2.2, R10.1, R17.1
unnamed: Q3.1, R21.1
unnamed: Q4.1, R33.2, R34.1
unnamed: Q4.2, R1.1, R11.1
unnamed: Q5.1, R35.2, R36.1
unnamed: Q5.2, R12.1, R16.1
unnamed: Q6.1, R22.1
unnamed: Q7.1, R3.1
unnamed: Q8.1, R7.1
unnamed: Q9.1, R5.1
PA0: J4.2, U7.1
PA1: J4.3, U7.2
PA2: D3.2 (A), J4.4, U7.3
PA3: D1.2 (A), J4.5, U7.4
PA4: J4.6, U7.5
PA5: J4.7, U7.6
PA6: J4.8, J5.1, J9.1, SW1.1, SW2.1, SW3.1, SW4.1, U7.11
PA7: J4.9
PB0: J4.10, JP4.2 (B)
PB1: J4.11
PB2: J4.12
PB3: J4.13, J5.2, J9.2, SW1.2
PB4: J4.14, J5.3, J9.3, SW2.2
PB5: J4.15, J5.4, J9.4, SW3.2
PB6: J4.16, J5.5, J9.5, SW4.2
PB7: J4.17
PIA0: J28.11, U1.11 (Y4), U22.11
PIA1: J28.10, U1.10 (Y5), U22.10
Q: J1.35, J13.7, J19.35, JP1.1 (A), R9.1, R26.1, U9.16 (B2), U16.16 (B2)
Q_33: U5.38 (76_IOT30B), U9.4 (A2), U16.4 (A2), U17.38 (76_IOT30B)
RESET_33: R4.2, R5.2, R18.2, R22.2, U5.36 (42_IOB42B), U17.36 (42_IOB42B)
R_CVBS: C11.1, J24.4, R12.2
R_CVBS_33: J7.3, J10.3, J18.3, R35.1, U5.18 (18_IOL49B_LED3), U17.18 (18_IOL49B_LED3)
R/~W: J1.32, J2.7, J3.7, J13.18, J17.7, J19.32, R13.2, R19.2, U11.2 (A0), U15.2 (A0), U22.9
S0: J2.1, J3.1, J17.1, J28.1, U1.1 (A), U9.14 (B4), U16.14 (B4)
S0_33: U5.6 (15_IOL47A_LED0), U9.6 (A4), U16.6 (A4), U17.6 (15_IOL47A_LED0)
S1: J2.2, J3.2, J17.2, J28.2, U1.2 (B), U9.13 (B5), U16.13 (B5)
S1_33: U5.35 (41_IOB43A), U9.7 (A5), U16.7 (A5), U17.35 (41_IOB43A)
S2: J2.3, J3.3, J17.3, J28.3, U1.3 (C), U9.12 (B6), U16.12 (B6)
S2_33: U5.7 (16_IOL47B_LED1), U9.8 (A6), U16.8 (A6), U17.7 (16_IOL47B_LED1)
SERNT: J12.2, J15.2, U11.5 (A3), U15.5 (A3)
SND: J13.35
TSC: J1.39, J19.39
~CART: J12.1, J13.8, J15.1, JP1.2 (B), U11.6 (A4), U15.6 (A4)
~CTS: J13.32, J28.12, U1.12 (Y3), U2.22 (*OE)
~DATAEN: J2.5, J3.5, J17.5, U12.19 (CE), U14.19 (CE), U22.6
~EXTROM: U1.13 (Y2), U22.13
~FIRQ: J1.4, J19.4, Q3.3, Q8.3
~FS_33: U5.2 (74_IOT34B), U9.2 (A0), U16.2 (A0), U17.2 (74_IOT34B)
~FS/CART: J4.18, J8.1
~FS: J14.1, J16.1, U9.18 (B0), U16.18 (B0)
~HALT: J1.40, J13.3, J19.40, U11.8 (A6), U15.8 (A6)
~HS_33: U5.1 (73_IOT40A), U9.3 (A1), U16.3 (A1), U17.1 (73_IOT40A)
~HS: J4.40, J14.2, J16.2, JP3.2 (B), U9.17 (B1), U16.17 (B1)
~HS/SERNT: J8.2, JP3.1 (A), JP4.1 (A)
~IRQ: J1.3, J19.3, Q1.3, Q7.3
~MENEN: U22.3, U22.12
~MRD: U1.15 (Y0), U22.1
~NMI: J1.2, J13.4, J19.2, U11.9 (A7), U15.9 (A7)
~RESET: J1.37, J13.5, J19.37, Q6.3, Q9.3, U11.3 (A1), U15.3 (A1)
~ROM: U1.14 (Y1), U22.2
~SCS: J13.36, J28.9, U1.9 (Y6)
~SLENB: J2.4, J3.4, J13.40, J17.4, J28.6, U1.6 (G1), U11.4 (A2), U15.4 (A2)

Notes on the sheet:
ADDRMUX DAUGHTERBOARD
26-3136 / 20261043
26-3134B / 20261058
EXTERNAL KEYBOARD EXTENSION
HBDOS-CART
PIA0 / PIA1 (SC67331/MC6821) DAUGHTERBOARD
VIDEO COMPONENT HAT
